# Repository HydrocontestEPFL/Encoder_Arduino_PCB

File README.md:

# Encoder_Arduino_PCB

Basic PCB design to connect the encoder to an arduino nano more reliable than with wires. Also helps to avoid messy cabling.

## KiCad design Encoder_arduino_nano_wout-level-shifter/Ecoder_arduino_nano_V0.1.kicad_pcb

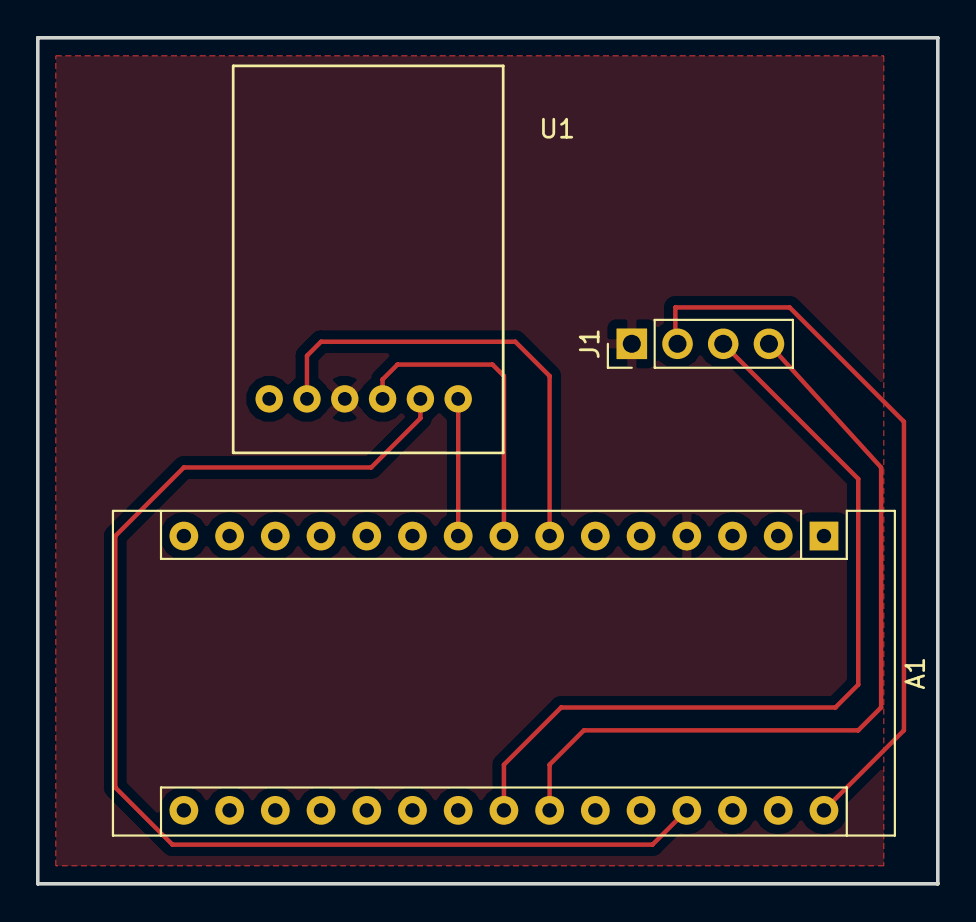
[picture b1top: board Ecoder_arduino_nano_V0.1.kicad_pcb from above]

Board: 2 copper layers, 50.0 x 47.0 mm, 3 parts (0 on the bottom side), 8 nets.

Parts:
A1: Arduino_Nano_v2.x; Arduino_Nano
J1: Conn_01x04_Female; PinHeader_1x04_P2.54mm_Vertical
U1: EMS22A_B-style

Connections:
GND: A1.4, J1.1, U1.3
unnamed: A1.7, U1.2
unnamed: A1.8, U1.4
unnamed: A1.9, U1.6
unnamed: A1.23, J1.3
unnamed: A1.24, J1.4
unnamed: A1.27, U1.5
unnamed: A1.30, J1.2

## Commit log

2019-06-08 Initial commit with a PCB not FINISHED
    Still need to verify the PCB if it is good or not. Also if it fits in the casing.
2019-06-17 Update files
